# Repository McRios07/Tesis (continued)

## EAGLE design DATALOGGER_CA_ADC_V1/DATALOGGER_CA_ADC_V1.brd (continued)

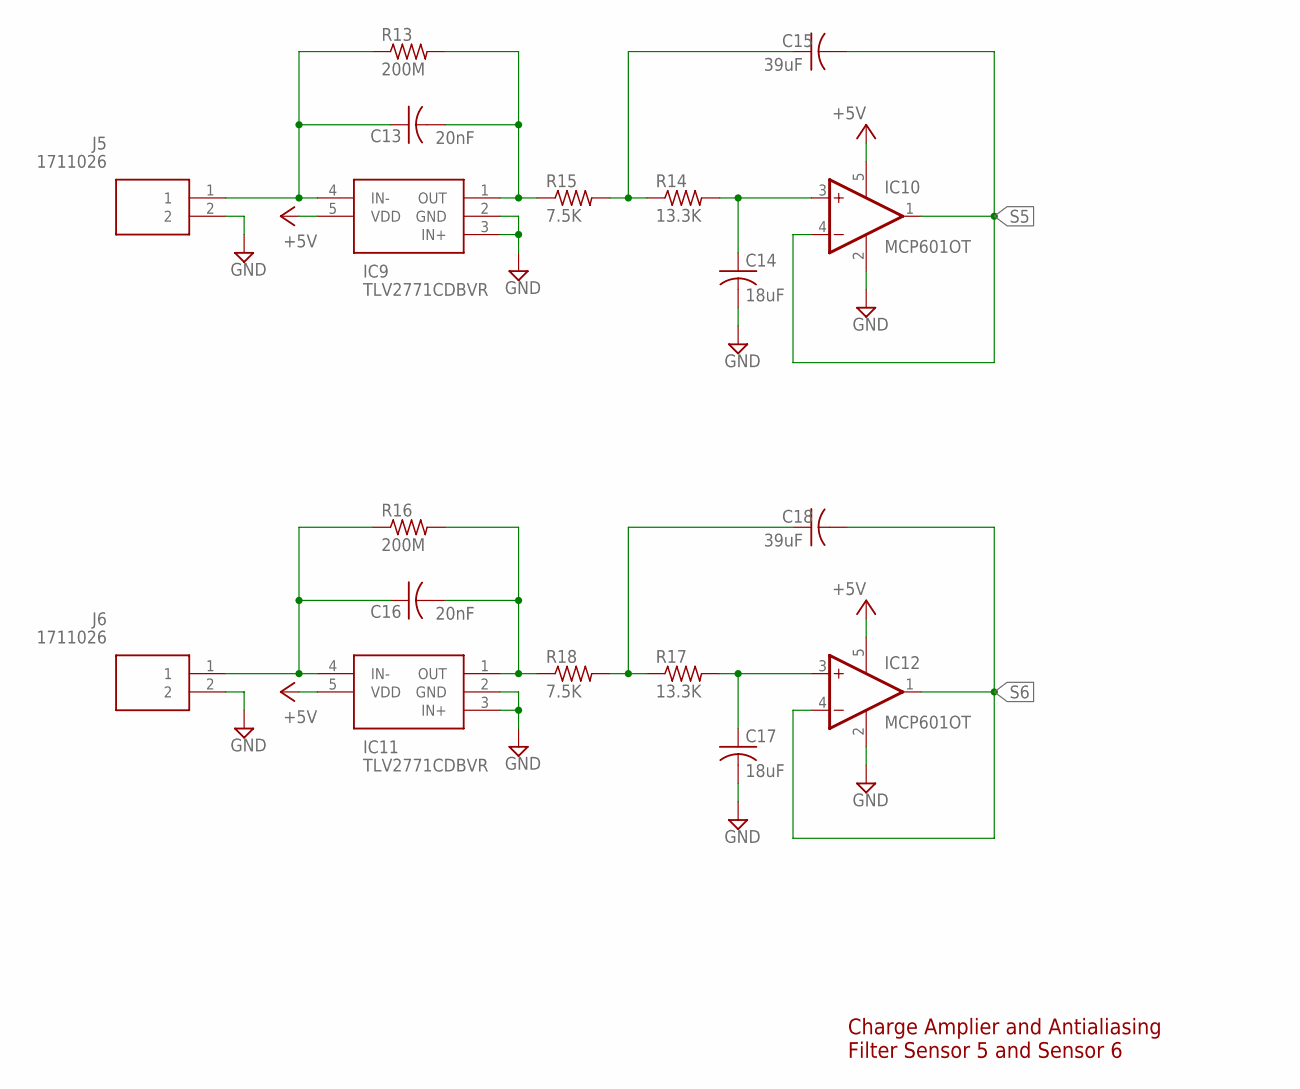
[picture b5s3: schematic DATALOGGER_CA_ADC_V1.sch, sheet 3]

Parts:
C13, C16: 20nF; C0805
C14, C17: 18uF; C0805
C15, C18: 39uF; C0805
IC9, IC11: TLV2771CDBVR; SOT95P280X145-5N
IC10, IC12: MCP601OT; SOT23-5
J5, J6: 1711026; SHDR2W110P0X500_1X2_1000X1120X
R13, R16: 200M; R0805
R14, R17: 13.3K; R0805
R15, R18: 7.5K; R0805

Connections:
+5V: IC9.5 (VDD), IC10.5 (V+), IC11.5 (VDD), IC12.5 (V+); also elsewhere on the board
GND: C14.2, C17.2, IC9.2 (GND), IC9.3 (IN+), IC10.2 (V-), IC11.2 (GND), IC11.3 (IN+), IC12.2 (V-), J5.2, J6.2; also elsewhere on the board
unnamed: C13.1, IC9.4 (IN-), J5.1, R13.1
unnamed: C13.2, IC9.1 (OUT), R13.2, R15.1
unnamed: C14.1, IC10.3 (+IN), R14.2
unnamed: C15.1, R14.1, R15.2
unnamed: C16.1, IC11.4 (IN-), J6.1, R16.1
unnamed: C16.2, IC11.1 (OUT), R16.2, R18.1
unnamed: C17.1, IC12.3 (+IN), R17.2
unnamed: C18.1, R17.1, R18.2
S5: C15.2, IC10.1 (OUT), IC10.4 (-IN); also elsewhere on the board
S6: C18.2, IC12.1 (OUT), IC12.4 (-IN); also elsewhere on the board

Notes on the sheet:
Charge Amplier and Antialiasing Filter Sensor 5 and Sensor 6

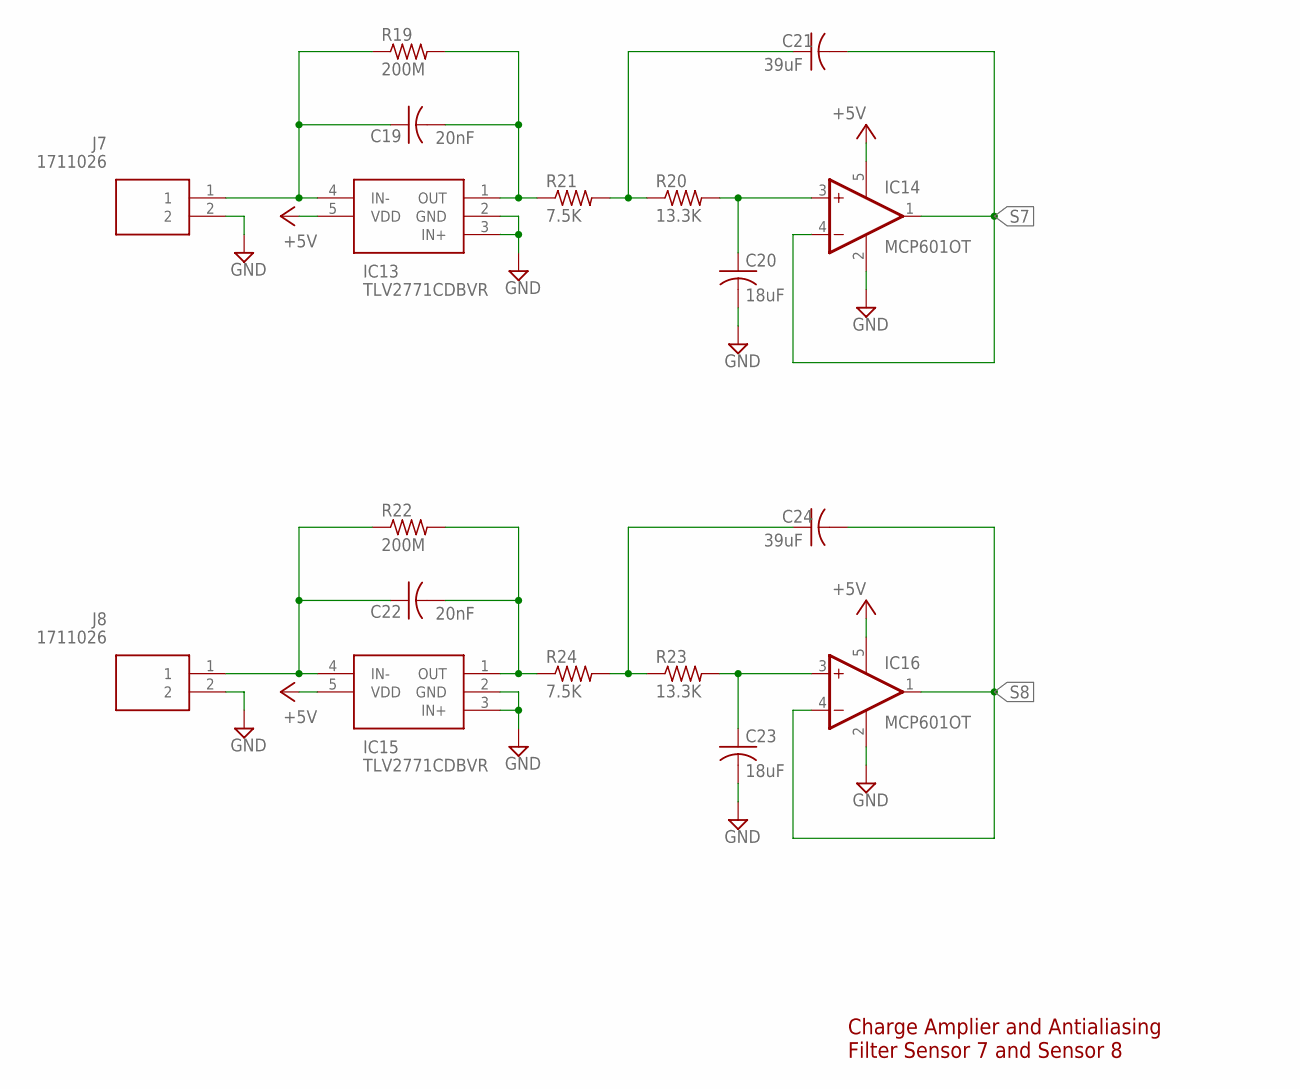
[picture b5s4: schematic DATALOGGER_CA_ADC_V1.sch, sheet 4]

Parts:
C19, C22: 20nF; C0805
C20, C23: 18uF; C0805
C21, C24: 39uF; C0805
IC13, IC15: TLV2771CDBVR; SOT95P280X145-5N
IC14, IC16: MCP601OT; SOT23-5
J7, J8: 1711026; SHDR2W110P0X500_1X2_1000X1120X
R19, R22: 200M; R0805
R20, R23: 13.3K; R0805
R21, R24: 7.5K; R0805

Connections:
+5V: IC13.5 (VDD), IC14.5 (V+), IC15.5 (VDD), IC16.5 (V+); also elsewhere on the board
GND: C20.2, C23.2, IC13.2 (GND), IC13.3 (IN+), IC14.2 (V-), IC15.2 (GND), IC15.3 (IN+), IC16.2 (V-), J7.2, J8.2; also elsewhere on the board
unnamed: C19.1, IC13.4 (IN-), J7.1, R19.1
unnamed: C19.2, IC13.1 (OUT), R19.2, R21.1
unnamed: C20.1, IC14.3 (+IN), R20.2
unnamed: C21.1, R20.1, R21.2
unnamed: C22.1, IC15.4 (IN-), J8.1, R22.1
unnamed: C22.2, IC15.1 (OUT), R22.2, R24.1
unnamed: C23.1, IC16.3 (+IN), R23.2
unnamed: C24.1, R23.1, R24.2
S7: C21.2, IC14.1 (OUT), IC14.4 (-IN); also elsewhere on the board
S8: C24.2, IC16.1 (OUT), IC16.4 (-IN); also elsewhere on the board

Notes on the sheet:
Charge Amplier and Antialiasing Filter Sensor 7 and Sensor 8

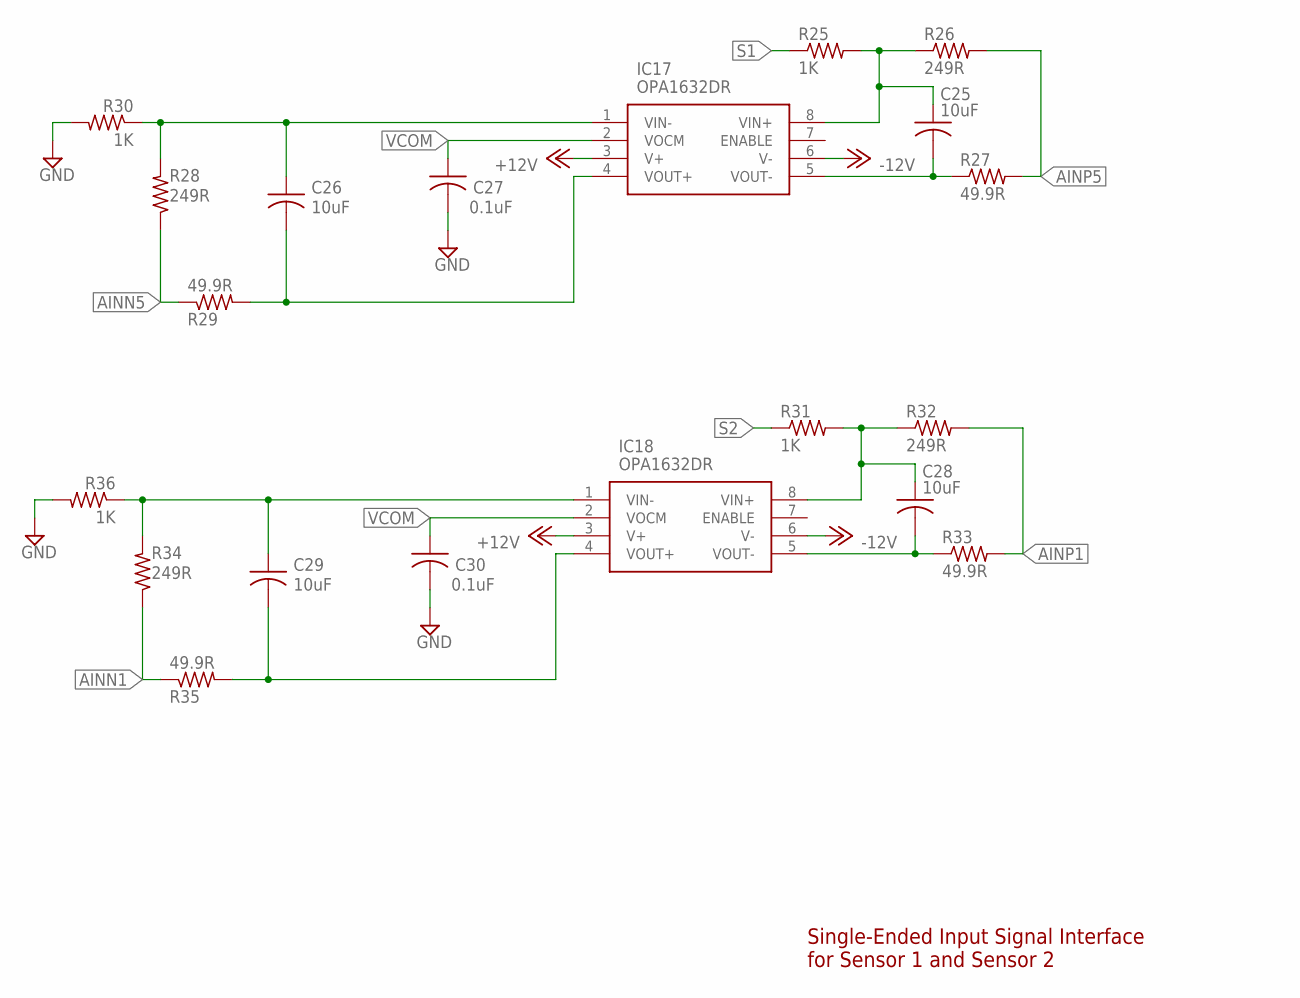
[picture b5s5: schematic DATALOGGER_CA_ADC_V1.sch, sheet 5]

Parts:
C25, C26, C28, C29: 10uF; C0805
C27, C30: 0.1uF; C0805
IC17, IC18: OPA1632DR; SOIC127P600X175-8N
R25, R30, R31, R36: 1K; R0805
R26, R28, R32, R34: 249R; R0805
R27, R29, R33, R35: 49.9R; R0805

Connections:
+12V: IC17.3 (V+), IC18.3 (V+); also elsewhere on the board
-12V: IC17.6 (V-), IC18.6 (V-); also elsewhere on the board
AINN1: R34.1, R35.1; also elsewhere on the board
AINN5: R28.1, R29.1; also elsewhere on the board
AINP1: R32.2, R33.2; also elsewhere on the board
AINP5: R26.2, R27.2; also elsewhere on the board
GND: C27.2, C30.2, R30.2, R36.2; also elsewhere on the board
unnamed: C25.1, IC17.8 (VIN+), R25.2, R26.1
unnamed: C25.2, IC17.5 (VOUT-), R27.1
unnamed: C26.1, IC17.1 (VIN-), R28.2, R30.1
unnamed: C28.1, IC18.8 (VIN+), R31.2, R32.1
unnamed: C26.2, IC17.4 (VOUT+), R29.2
unnamed: C28.2, IC18.5 (VOUT-), R33.1
unnamed: C29.1, IC18.1 (VIN-), R34.2, R36.1
unnamed: C29.2, IC18.4 (VOUT+), R35.2
S1: R25.1; also elsewhere on the board
S2: R31.1; also elsewhere on the board
VCOM: C27.1, C30.1, IC17.2 (VOCM), IC18.2 (VOCM); also elsewhere on the board

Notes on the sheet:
Single-Ended Input Signal Interface for Sensor 1 and Sensor 2

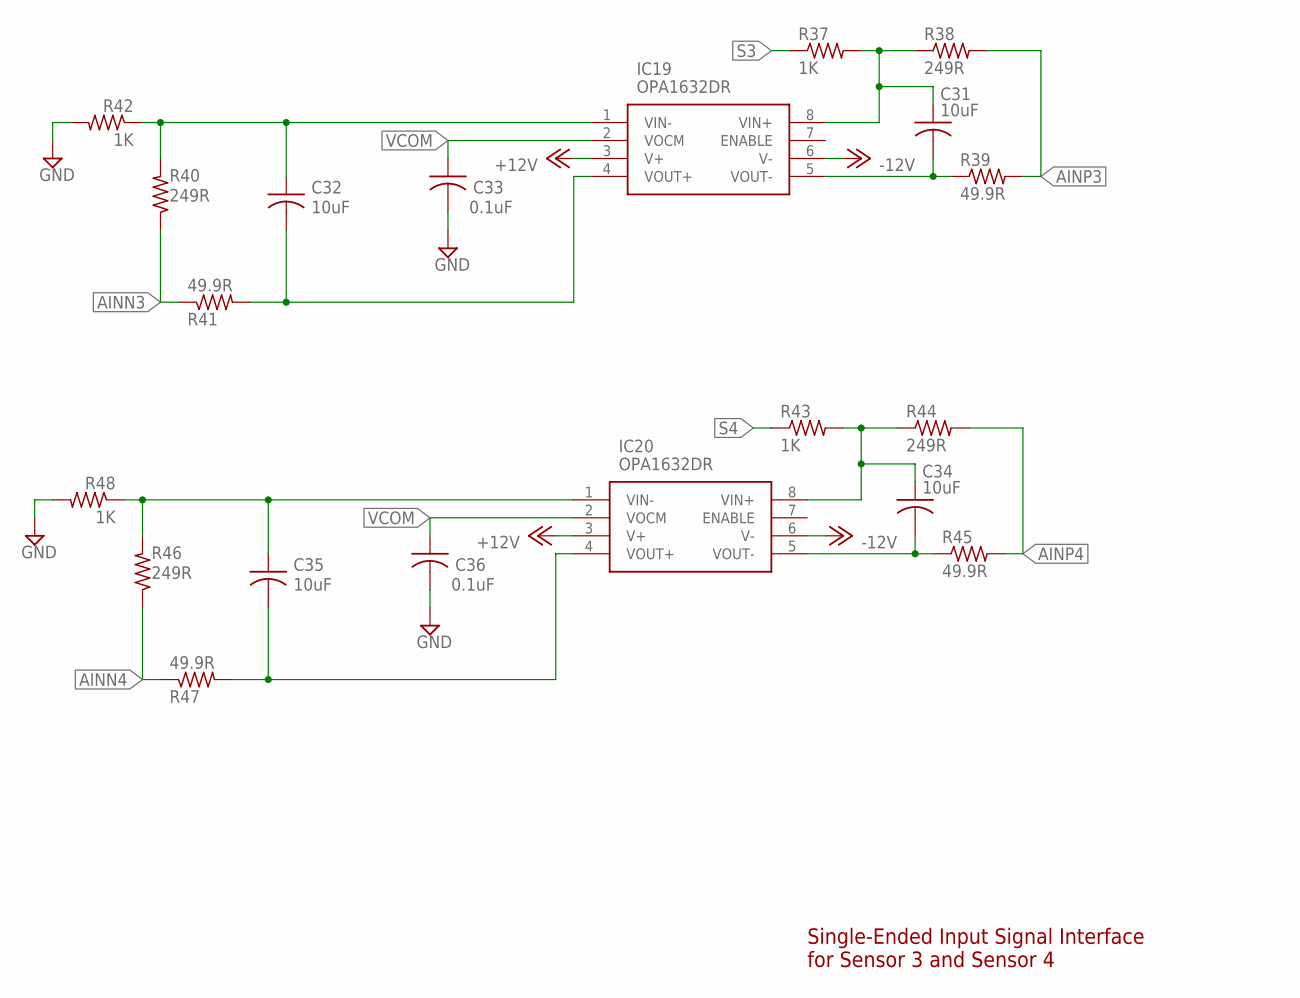
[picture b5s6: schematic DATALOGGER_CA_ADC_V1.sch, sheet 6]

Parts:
C31, C32, C34, C35: 10uF; C0805
C33, C36: 0.1uF; C0805
IC19, IC20: OPA1632DR; SOIC127P600X175-8N
R37, R42, R43, R48: 1K; R0805
R38, R40, R44, R46: 249R; R0805
R39, R41, R45, R47: 49.9R; R0805

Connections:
+12V: IC19.3 (V+), IC20.3 (V+); also elsewhere on the board
-12V: IC19.6 (V-), IC20.6 (V-); also elsewhere on the board
AINN3: R40.1, R41.1; also elsewhere on the board
AINN4: R46.1, R47.1; also elsewhere on the board
AINP3: R38.2, R39.2; also elsewhere on the board
AINP4: R44.2, R45.2; also elsewhere on the board
GND: C33.2, C36.2, R42.2, R48.2; also elsewhere on the board
unnamed: C31.1, IC19.8 (VIN+), R37.2, R38.1
unnamed: C31.2, IC19.5 (VOUT-), R39.1
unnamed: C32.1, IC19.1 (VIN-), R40.2, R42.1
unnamed: C32.2, IC19.4 (VOUT+), R41.2
unnamed: C34.1, IC20.8 (VIN+), R43.2, R44.1
unnamed: C34.2, IC20.5 (VOUT-), R45.1
unnamed: C35.1, IC20.1 (VIN-), R46.2, R48.1
unnamed: C35.2, IC20.4 (VOUT+), R47.2
S3: R37.1; also elsewhere on the board
S4: R43.1; also elsewhere on the board
VCOM: C33.1, C36.1, IC19.2 (VOCM), IC20.2 (VOCM); also elsewhere on the board

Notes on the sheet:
Single-Ended Input Signal Interface for Sensor 3 and Sensor 4

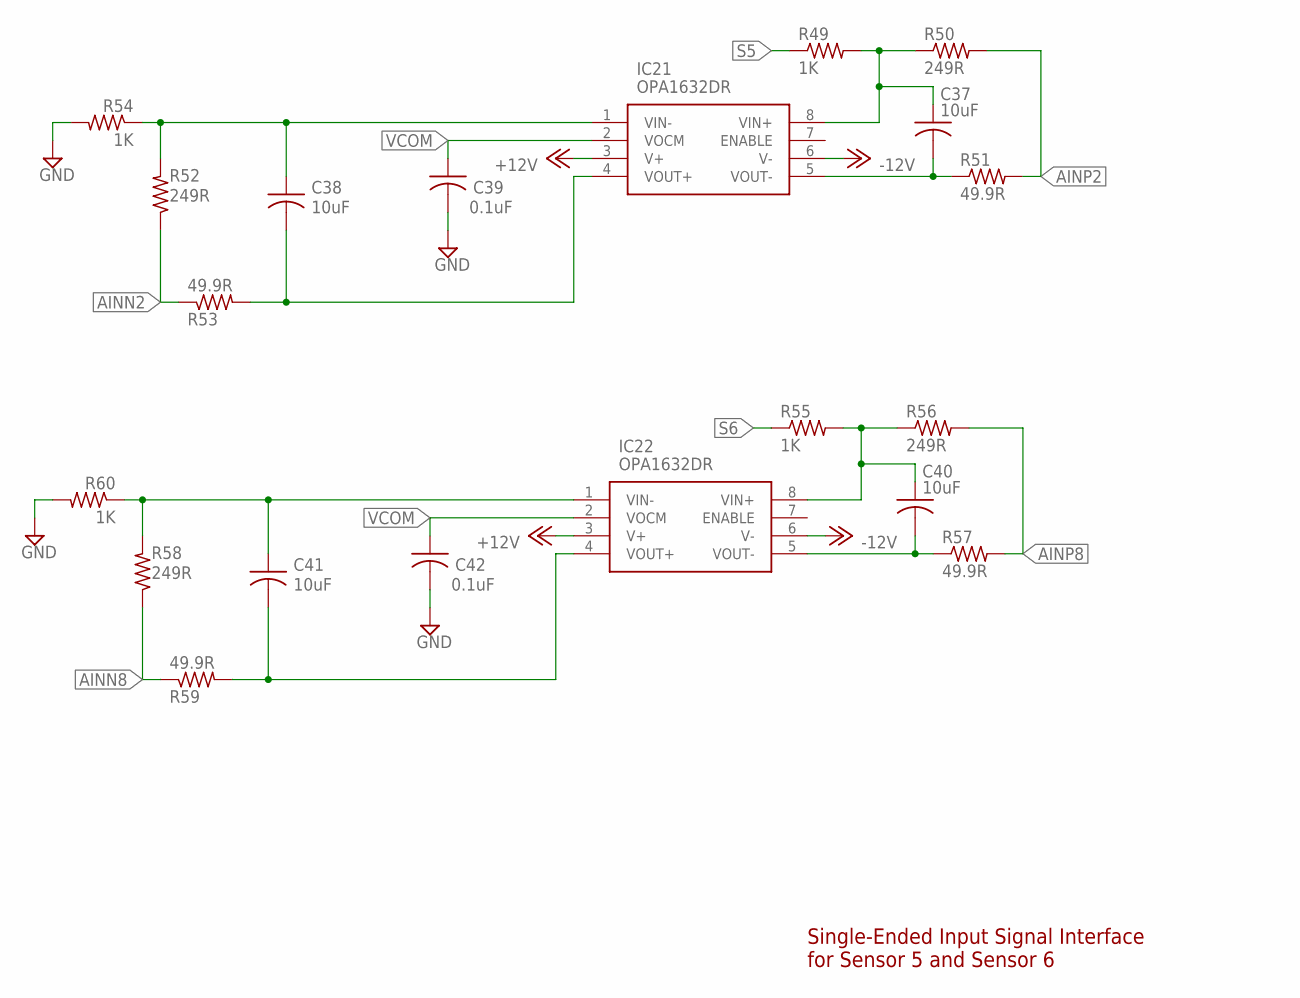
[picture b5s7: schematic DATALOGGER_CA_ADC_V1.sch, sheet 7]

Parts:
C37, C38, C40, C41: 10uF; C0805
C39, C42: 0.1uF; C0805
IC21, IC22: OPA1632DR; SOIC127P600X175-8N
R49, R54, R55, R60: 1K; R0805
R50, R52, R56, R58: 249R; R0805
R51, R53, R57, R59: 49.9R; R0805

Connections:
+12V: IC21.3 (V+), IC22.3 (V+); also elsewhere on the board
-12V: IC21.6 (V-), IC22.6 (V-); also elsewhere on the board
AINN2: R52.1, R53.1; also elsewhere on the board
AINN8: R58.1, R59.1; also elsewhere on the board
AINP2: R50.2, R51.2; also elsewhere on the board
AINP8: R56.2, R57.2; also elsewhere on the board
GND: C39.2, C42.2, R54.2, R60.2; also elsewhere on the board
unnamed: C37.1, IC21.8 (VIN+), R49.2, R50.1
unnamed: C37.2, IC21.5 (VOUT-), R51.1
unnamed: C38.1, IC21.1 (VIN-), R52.2, R54.1
unnamed: C38.2, IC21.4 (VOUT+), R53.2
unnamed: C40.1, IC22.8 (VIN+), R55.2, R56.1
unnamed: C40.2, IC22.5 (VOUT-), R57.1
unnamed: C41.1, IC22.1 (VIN-), R58.2, R60.1
unnamed: C41.2, IC22.4 (VOUT+), R59.2
S5: R49.1; also elsewhere on the board
S6: R55.1; also elsewhere on the board
VCOM: C39.1, C42.1, IC21.2 (VOCM), IC22.2 (VOCM); also elsewhere on the board

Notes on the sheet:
Single-Ended Input Signal Interface for Sensor 5 and Sensor 6

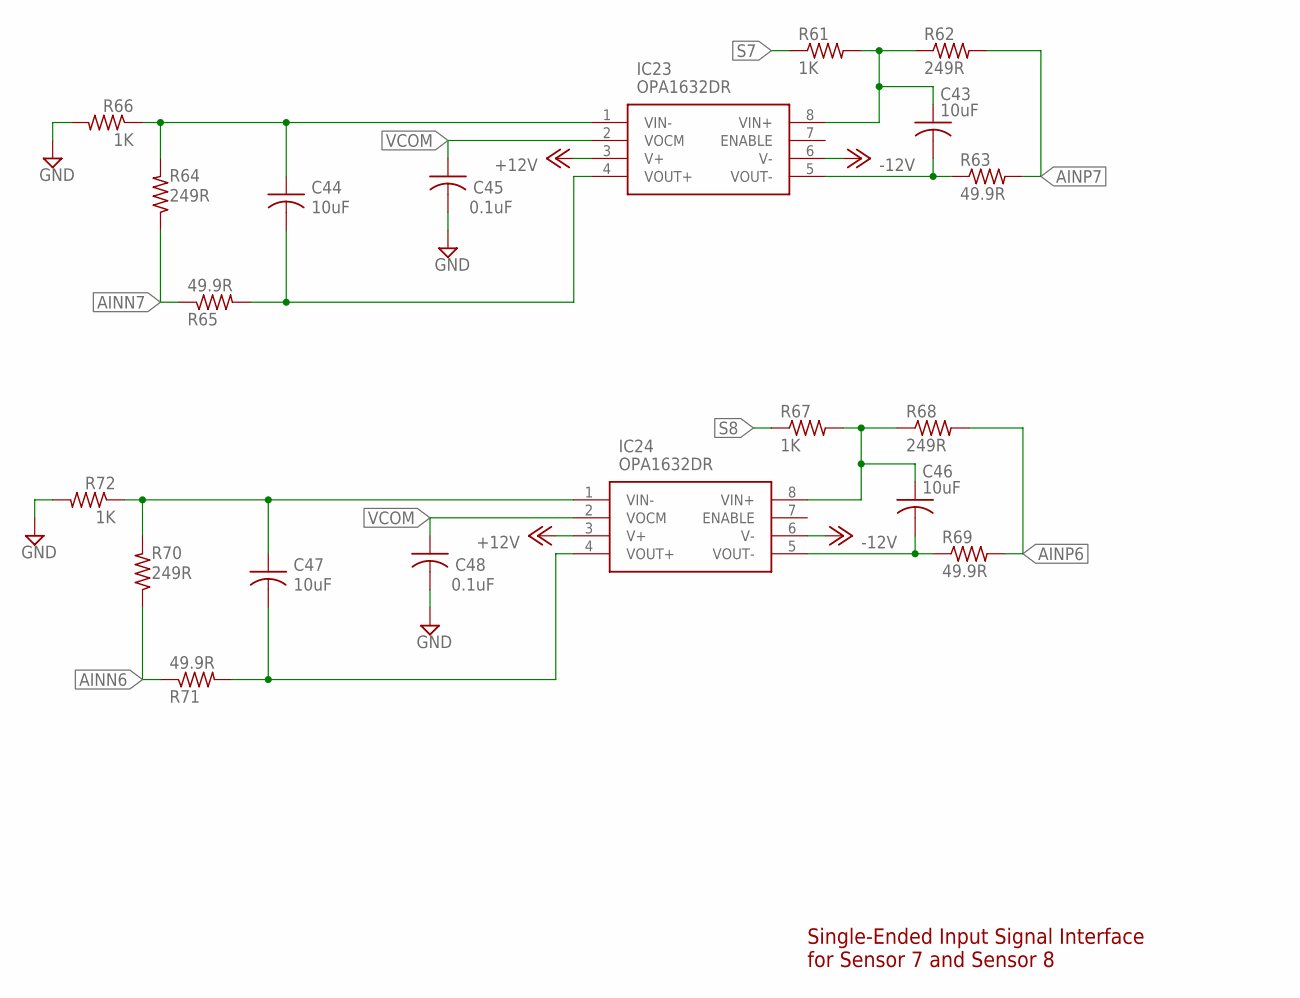
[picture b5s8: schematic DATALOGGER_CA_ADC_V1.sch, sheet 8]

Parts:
C43, C44, C46, C47: 10uF; C0805
C45, C48: 0.1uF; C0805
IC23, IC24: OPA1632DR; SOIC127P600X175-8N
R61, R66, R67, R72: 1K; R0805
R62, R64, R68, R70: 249R; R0805
R63, R65, R69, R71: 49.9R; R0805

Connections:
+12V: IC23.3 (V+), IC24.3 (V+); also elsewhere on the board
-12V: IC23.6 (V-), IC24.6 (V-); also elsewhere on the board
AINN6: R70.1, R71.1; also elsewhere on the board
AINN7: R64.1, R65.1; also elsewhere on the board
AINP6: R68.2, R69.2; also elsewhere on the board
AINP7: R62.2, R63.2; also elsewhere on the board
GND: C45.2, C48.2, R66.2, R72.2; also elsewhere on the board
unnamed: C43.1, IC23.8 (VIN+), R61.2, R62.1
unnamed: C43.2, IC23.5 (VOUT-), R63.1
unnamed: C44.1, IC23.1 (VIN-), R64.2, R66.1
unnamed: C44.2, IC23.4 (VOUT+), R65.2
unnamed: C46.1, IC24.8 (VIN+), R67.2, R68.1
unnamed: C46.2, IC24.5 (VOUT-), R69.1
unnamed: C47.1, IC24.1 (VIN-), R70.2, R72.1
unnamed: C47.2, IC24.4 (VOUT+), R71.2
S7: R61.1; also elsewhere on the board
S8: R67.1; also elsewhere on the board
VCOM: C45.1, C48.1, IC23.2 (VOCM), IC24.2 (VOCM); also elsewhere on the board

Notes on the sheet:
Single-Ended Input Signal Interface for Sensor 7 and Sensor 8

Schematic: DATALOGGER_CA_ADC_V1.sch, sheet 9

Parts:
JP1, JP2: PINHD-2X10; 2X10

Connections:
+1V8: JP1.19, JP1.20; also elsewhere on the board
+3V3: JP1.17, JP1.18; also elsewhere on the board
+5V: JP1.13, JP1.14; also elsewhere on the board
+12V: JP1.1, JP1.2; also elsewhere on the board
+24V: JP1.9, JP1.10
-12V: JP1.5, JP1.6; also elsewhere on the board
CLK: JP2.9; also elsewhere on the board
DOUT1: JP2.10; also elsewhere on the board
DOUT2: JP2.7; also elsewhere on the board
DOUT3: JP2.8; also elsewhere on the board
DOUT4: JP2.5; also elsewhere on the board
DOUT5: JP2.6; also elsewhere on the board
DOUT6: JP2.3; also elsewhere on the board
DOUT7: JP2.4; also elsewhere on the board
DOUT8: JP2.1; also elsewhere on the board
DRDY: JP2.11; also elsewhere on the board
GND: JP1.3, JP1.4, JP1.7, JP1.8, JP1.11, JP1.12, JP1.15, JP1.16, JP2.13, JP2.14, JP2.15, JP2.16, JP2.17, JP2.18, JP2.19, JP2.20; also elsewhere on the board
SCLK: JP2.12; also elsewhere on the board
SYNC: JP2.2; also elsewhere on the board

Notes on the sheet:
Inputs and Outputs

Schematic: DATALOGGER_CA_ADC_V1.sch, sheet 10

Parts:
C49: 100uF; C1206
C50, C51, C53, C54: 0.1uF; C0805
C52: 10uF; C0805
C55, C56, C57, C58, C59, C60, C61, C62: 2.2nF; C0805
IC25: REF1004U; SO08
R73: 20K; R0805
R74, R76: 1K; R0805
R75, R77, R78: 100R; R0805
U1, U2: OPA350EA/2K5; DGK8_TEX

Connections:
+5V: R73.2, U1.7 (V+), U2.7 (V+); also elsewhere on the board
AINN1: C55.2; also elsewhere on the board
AINN2: C56.2; also elsewhere on the board
AINN3: C57.2; also elsewhere on the board
AINN4: C58.2; also elsewhere on the board
AINN5: C59.2; also elsewhere on the board
AINN6: C60.2; also elsewhere on the board
AINN7: C61.2; also elsewhere on the board
AINN8: C62.2; also elsewhere on the board
AINP1: C55.1; also elsewhere on the board
AINP2: C56.1; also elsewhere on the board
AINP3: C57.1; also elsewhere on the board
AINP4: C58.1; also elsewhere on the board
AINP5: C59.1; also elsewhere on the board
AINP6: C60.1; also elsewhere on the board
AINP7: C61.1; also elsewhere on the board
AINP8: C62.1; also elsewhere on the board
GND: C49.2, C50.2, C52.2, C53.2, C54.2, IC25.4 (A), U1.4 (V-), U2.4 (V-); also elsewhere on the board
unnamed: IC25.8 (C1), R73.1
unnamed: IC25.6 (C), R74.1
unnamed: C49.1, C50.1, R74.2, R75.1
unnamed: R75.2, U2.3 (IN+)
unnamed: C51.2, R77.1, U2.6 (OUTPUT)
unnamed: C51.1, R76.1, U2.2 (IN-)
unnamed: R78.1, U1.2 (IN-), U1.6 (OUTPUT)
VCOM: R78.2; also elsewhere on the board
VCOMM: C54.1, U1.3 (IN+); also elsewhere on the board
VREFP: C52.1, C53.1, R76.2, R77.2; also elsewhere on the board

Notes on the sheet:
Voltage References for ADS

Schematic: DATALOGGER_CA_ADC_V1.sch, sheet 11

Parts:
C63, C64, C65: 10uF; C0805
SJ1: SJ2W; SJ_2
U3: ADS1178IPAPT; PAP64_TEX

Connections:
+1V8: C65.1, U3.26 (DVDD); also elsewhere on the board
+3V3: C64.1, SJ1.1, U3.10 (CLKDIV), U3.22 (IOVDD_2), U3.23 (IOVDD), U3.31 (FORMAT1); also elsewhere on the board
+5V: C63.1, U3.5 (AVDD_2), U3.44 (AVDD_3), U3.60 (AVDD); also elsewhere on the board
AINN1: U3.4 (AINN1); also elsewhere on the board
AINN2: U3.2 (AINN2); also elsewhere on the board
AINN3: U3.64 (AINN3); also elsewhere on the board
AINN4: U3.62 (AINN4); also elsewhere on the board
AINN5: U3.52 (AINN5); also elsewhere on the board
AINN6: U3.50 (AINN6); also elsewhere on the board
AINN7: U3.48 (AINN7); also elsewhere on the board
AINN8: U3.46 (AINN8); also elsewhere on the board
AINP1: U3.3 (AINP1); also elsewhere on the board
AINP2: U3.1 (AINP2); also elsewhere on the board
AINP3: U3.63 (AINP3); also elsewhere on the board
AINP4: U3.61 (AINP4); also elsewhere on the board
AINP5: U3.51 (AINP5); also elsewhere on the board
AINP6: U3.49 (AINP6); also elsewhere on the board
AINP7: U3.47 (AINP7); also elsewhere on the board
AINP8: U3.45 (AINP8); also elsewhere on the board
CLK: U3.27 (CLK); also elsewhere on the board
DOUT1: U3.20 (DOUT1); also elsewhere on the board
DOUT2: U3.19 (DOUT2); also elsewhere on the board
DOUT3: U3.18 (DOUT3); also elsewhere on the board
DOUT4: U3.17 (DOUT4); also elsewhere on the board
DOUT5: U3.16 (DOUT5); also elsewhere on the board
DOUT6: U3.15 (DOUT6); also elsewhere on the board
DOUT7: U3.14 (DOUT7); also elsewhere on the board
DOUT8: U3.13 (DOUT8); also elsewhere on the board
DRDY: U3.29 (!DRDY/FSYNC); also elsewhere on the board
GND: C63.2, C64.2, C65.2, SJ1.3, U3.6 (AGND_2), U3.7 (DGND_2), U3.8 (TEST0), U3.9 (TEST1), U3.12 (DIN), U3.21 (DGND_3), U3.24 (DGND_4), U3.25 (DGND), U3.30 (FORMAT2), U3.32 (FORMAT0), U3.34 (MODE), U3.43 (AGND_3), U3.53 (AVDD_4), U3.54 (AGND_4), U3.57 (VREFN), U3.58 (AGND_5), U3.59 (AGND), U3.EPAD; also elsewhere on the board
unnamed: SJ1.2, U3.35 (!PWDN8), U3.36 (!PWDN7), U3.37 (!PWDN6), U3.38 (!PWDN5), U3.39 (!PWDN4), U3.40 (!PWDN3), U3.41 (!PWDN2), U3.42 (!PWDN1)
SCLK: U3.28 (SCLK); also elsewhere on the board
SYNC: U3.11 (!SYNC); also elsewhere on the board
VCOMM: U3.55 (VCOM); also elsewhere on the board
VREFP: U3.56 (VREFP); also elsewhere on the board

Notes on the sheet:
ADS connection

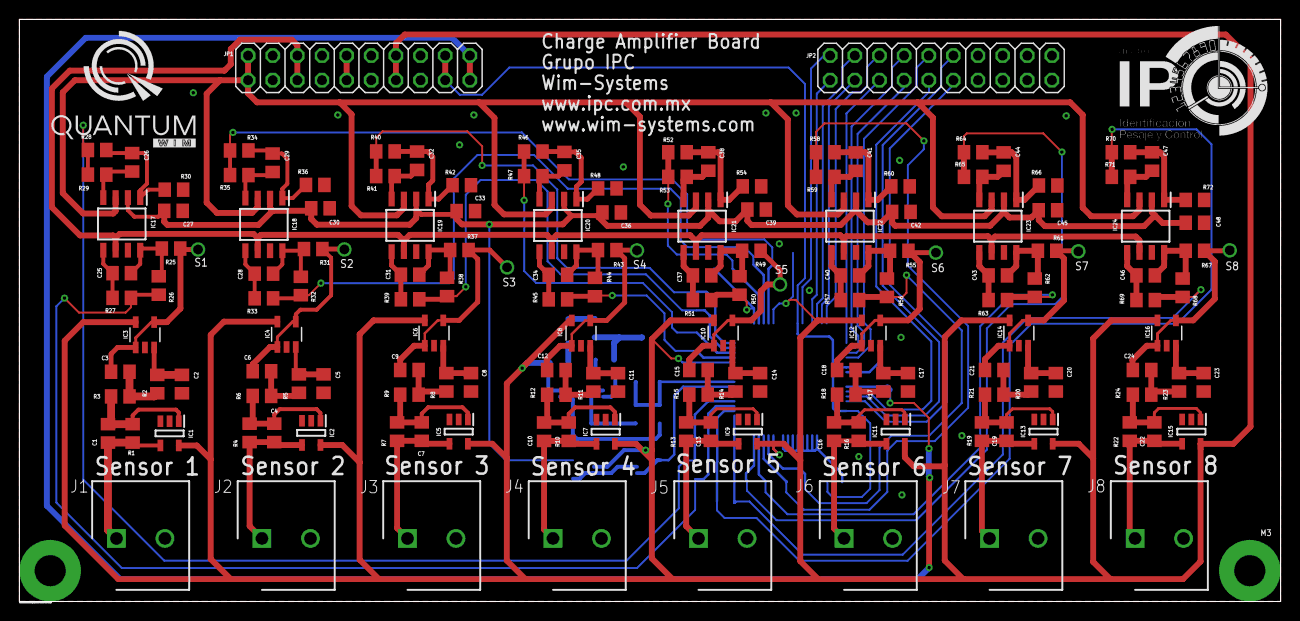
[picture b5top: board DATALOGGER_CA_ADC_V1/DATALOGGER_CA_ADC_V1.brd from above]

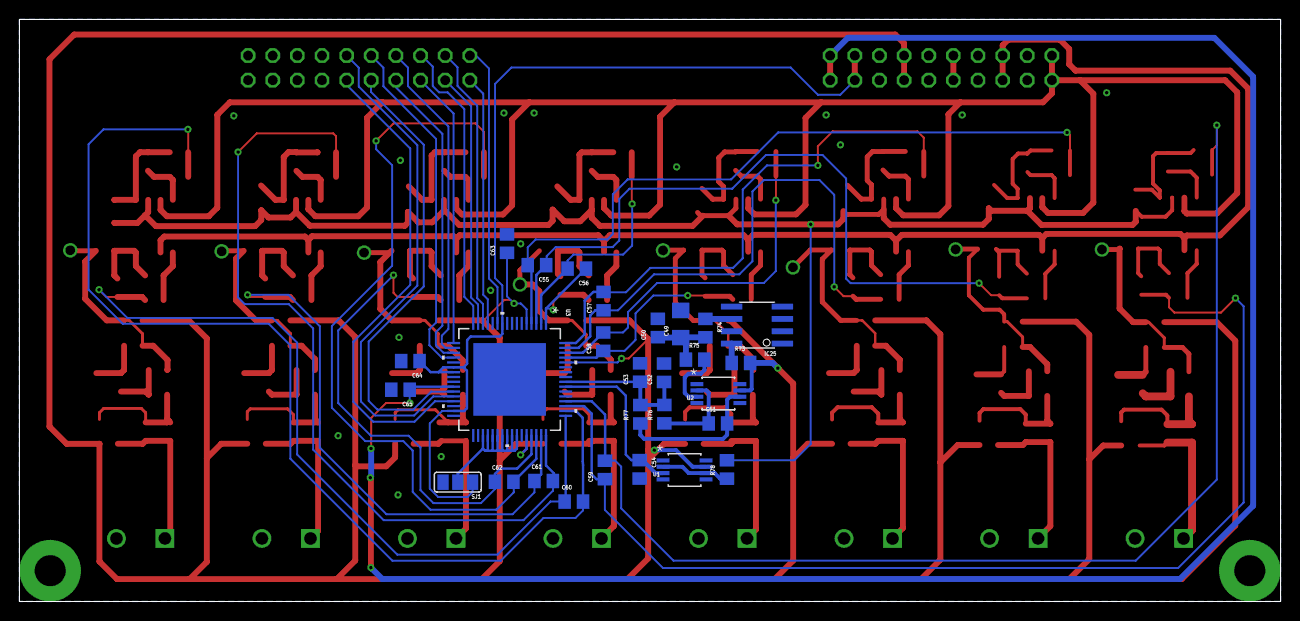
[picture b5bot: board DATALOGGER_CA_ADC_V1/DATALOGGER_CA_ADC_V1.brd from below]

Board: 2 copper layers, 130.0 x 60.0 mm, 182 parts (28 on the bottom side), 118 nets.

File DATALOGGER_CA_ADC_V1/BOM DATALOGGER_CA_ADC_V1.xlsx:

|  |  | BOM DATALOGGER_CA_ADC_V1 (Sample Bill of Materials)
Item # | *Designator | *Qty | Manufacturer | *Mfg Part # | Description / Value | *Package/Footprint | Type | Your Instructions / Notes
1 | JP1 | 1 |  | SFH11-PBPC-D10-RA-BK | 20 Position Header Connector Through Hole, Right Angle | 2X10 | Through Hole
2 | JP2 | 1 |  | ESQ-110-14-T-D | 20 Position Elevated Socket Connector Through Hole | 2X10 | Through Hole
3 | SJ1 | 1 |  |  |  |  |  | no device connected
4 | C27, C30, C33, C36, C39, C42, C45, C48, C50, C51, C53, C54 | 12 |  | Generic | 0.1µF ±10% 50V Ceramic Capacitor X7R 0805 (2012 Metric) | 0805 | SMD
5 | R75, R77, R78 | 3 |  | Generic | 100 Ohms ±0.1% 0.125W, 1/8W Chip Resistor 0805 (2012 Metric) Automotive AEC-Q20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 | 0805 | SMD
6 | C49 | 1 |  | Generic | 100µF ±20% 4V Ceramic Capacitor X6S 0805 (2012 Metric) | 1206 | SMD
7 | C25, C26, C28, C29, C31, C32, C34, C35, C37, C38, C40, C41, C43, C44, C46, C47,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 | 20 |  | Generic | 10µF ±10% 6.3V Ceramic Capacitor X5R 0805 (2012 Metric) | 0805 | SMD
8 | R2, R5, R8, R11, R14, R17, R20, R23 | 8 |  | RC0805FR-0713K3L | 13.3 kOhms ±1% 0.125W, 1/8W Chip Resistor 0805 (2012 Metric) Moisture Resistant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 | 0805 | SMD
9 | J1, J2, J3, J4, J5, J6, J7, J8 | 8 |  | 1711026 | 2 Position Wire to Board Terminal Block Horizontal with Board 0.197" (5.00mm) T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 | 1711026 | Through Hole
10 | C2, C5, C8, C11, C14, C17, C20, C23 | 8 |  | C0805C183K5RACTU | 0.018µF ±10% 50V Ceramic Capacitor X7R 0805 (2012 Metric) | 0805 | SMD
11 | R25, R30, R31, R36, R37, R42, R43, R48, R49, R54, R55, R60, R61, R66, R67, R72,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 | 18 |  | Generic | 1 kOhms ±1% 0.125W, 1/8W Chip Resistor 0805 (2012 Metric) Moisture Resistant Th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 | 0805 | SMD
12 | C55, C56, C57, C58, C59, C60, C61, C62 | 8 |  | GRM2165C1H222JA01D | 2200pF ±5% 50V Ceramic Capacitor C0G, NP0 0805 (2012 Metric) | 0805 | SMD
13 | R1, R4, R7, R10, R13, R16, R19, R22 | 8 |  | HMC0805JT200M | 200 MOhms ±5% 0.125W, 1/8W Chip Resistor 0805 (2012 Metric) Thick Film | 0805 | SMD
14 | R73 | 1 |  | Generic | 20 kOhms ±1% 0.125W, 1/8W Chip Resistor 0805 (2012 Metric) Moisture Resistant T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 | 0805 | SMD
15 | C1, C4, C7, C10, C13, C16, C19, C22 | 8 |  | Generic | 0.02µF ±5% 50V Ceramic Capacitor C0G, NP0 0805 (2012 Metric) | 0805 | SMD
16 | R26, R28, R32, R34, R38, R40, R44, R46, R50, R52, R56, R58, R62, R64, R68, R70 | 16 |  | RC0805FR-07249RL | 249 Ohms ±1% 0.125W, 1/8W Chip Resistor 0805 (2012 Metric) Moisture Resistant T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 | 0805 | SMD
17 | C3, C6, C9, C12, C15, C18, C21, C24 | 8 |  | C0805C393J5RACTU | 0.039µF ±5% 50V Ceramic Capacitor X7R 0805 (2012 Metric) | 0805 | SMD
18 | R27, R29, R33, R35, R39, R41, R45, R47, R51, R53, R57, R59, R63, R65, R69, R71 | 16 |  | ERJ-6ENF49R9V | 49.9 Ohms ±1% 0.125W, 1/8W Chip Resistor 0805 (2012 Metric) Automotive AEC-Q200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 | 0805 | SMD
19 | R3, R6, R9, R12, R15, R18, R21, R24 | 8 |  | CRG0805F7K5 | 7.5 kOhms ±1% 0.125W, 1/8W Chip Resistor 0805 (2012 Metric) Thick Film | 0805 | SMD
20 | U3 | 1 |  | ADS1178IPAPT | 16 Bit Analog to Digital Converter 8 Input 1 Sigma-Delta 64-HTQFP (10x10) | 64-HTQFP | SMD
21 | IC3, IC4, IC6, IC8, IC10, IC12, IC14, IC16 | 8 |  | MCP601T-I/OT | General Purpose Amplifier 1 Circuit Rail-to-Rail SOT-23-5 | SOT-23-5 | SMD
22 | IC17, IC18, IC19, IC20, IC21, IC22, IC23, IC24 | 8 |  | OPA1632DR | Audio Amplifier 1 Circuit Differential 8-SOIC | 8-SOIC | SMD
23 | U1, U2 | 2 |  | OPA350EA/2K5 | General Purpose Amplifier 1 Circuit Rail-to-Rail 8-VSSOP | 8-VSSOP | SMD
24 | IC25 | 1 |  | REF1004C-2.5 | Shunt Voltage Reference IC ±0.4% 8-SOIC | 8-SOIC | SMD
25 | IC1, IC2, IC5, IC7, IC9, IC11, IC13, IC15 | 8 |  | TLV2771CDBVR | General Purpose Amplifier 1 Circuit Rail-to-Rail SOT-23-5 | SOT-23-5 | SMD

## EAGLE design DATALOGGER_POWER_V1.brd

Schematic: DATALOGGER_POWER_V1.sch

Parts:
C1: 470uF; E5-13
C2: 1000uF; CAP_UCD_16X16P5_NCH
C3: 10uF; C1206
C4: 3.3uF; E2-4
C5, C7, C9: 10 uF; C1206
C6, C10: 390uF; E2-4
C8: 100 nF; C1206
D1: 1N5819-B; DO41-7.6
D2: LEDCHIPLED_1206; CHIPLED_1206
IC1: MIC4576-5.0WT; TO170P470X1016X1600-5P
IC2: TMH2412D
J1: +24V; SHDR2W110P0X500_1X2_1000X1120X
L1: 33uH; HCMA1707-330-R
L2, L3: 4.7uH; SRN4018
PS1: PAM2306AYPKE; SON45P300X300X80-13N
R1, R3: 0R; R1206
R2: 330; R1206
R5: 100K; R1206
SV1: MA10-2

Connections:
+1V8: C5.1, L2.2, R1.1, SV1.19, SV1.20
+3V3: C7.1, L3.2, R3.2, SV1.17, SV1.18
+5V: C2.1, C3.1, C9.1, IC1.4 (FB), L1.2, PS1.1 (VIN2), PS1.6 (EN1), PS1.7 (VIN1), R2.1, R5.1, SV1.13, SV1.14
+12V: C6.+, IC2.6 (+VOUT), SV1.1, SV1.2
+24V: C1.+, C4.+, IC1.1 (VIN), IC2.1 (VCC), J1.1, SV1.9, SV1.10
-12V: C10.+, IC2.4 (-VOUT), SV1.5, SV1.6
GND: C1.-, C2.2, C3.2, C4.-, C5.2, C6.-, C7.2, C8.2, C9.2, C10.-, D1.A, D2.C, IC1.3 (GND), IC1.5 (SHDN), IC2.2 (GND), IC2.5 (COM), J1.2, PS1.3 (GND_1), PS1.9 (GND_2), PS1.13 (GND_3), SV1.3, SV1.4, SV1.7, SV1.8, SV1.11, SV1.12, SV1.15, SV1.16
unnamed: D2.A, R2.2
unnamed: D1.C, IC1.2 (SW), L1.1
unnamed: L3.1, PS1.8 (LX1)
unnamed: L2.1, PS1.2 (LX2)
unnamed: PS1.10 (FB2), R1.2
unnamed: PS1.4 (FB1), R3.1
unnamed: C8.1, PS1.12 (EN2), R5.2

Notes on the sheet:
POWER SUPPLY

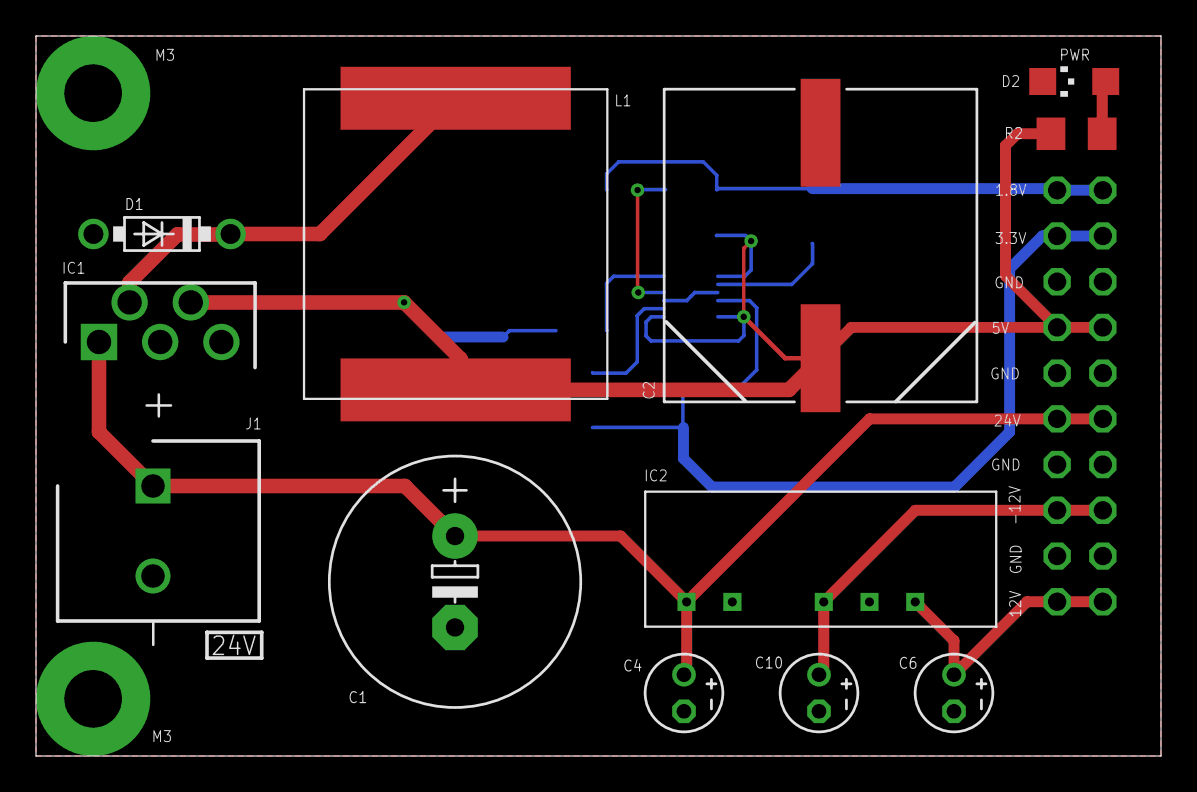
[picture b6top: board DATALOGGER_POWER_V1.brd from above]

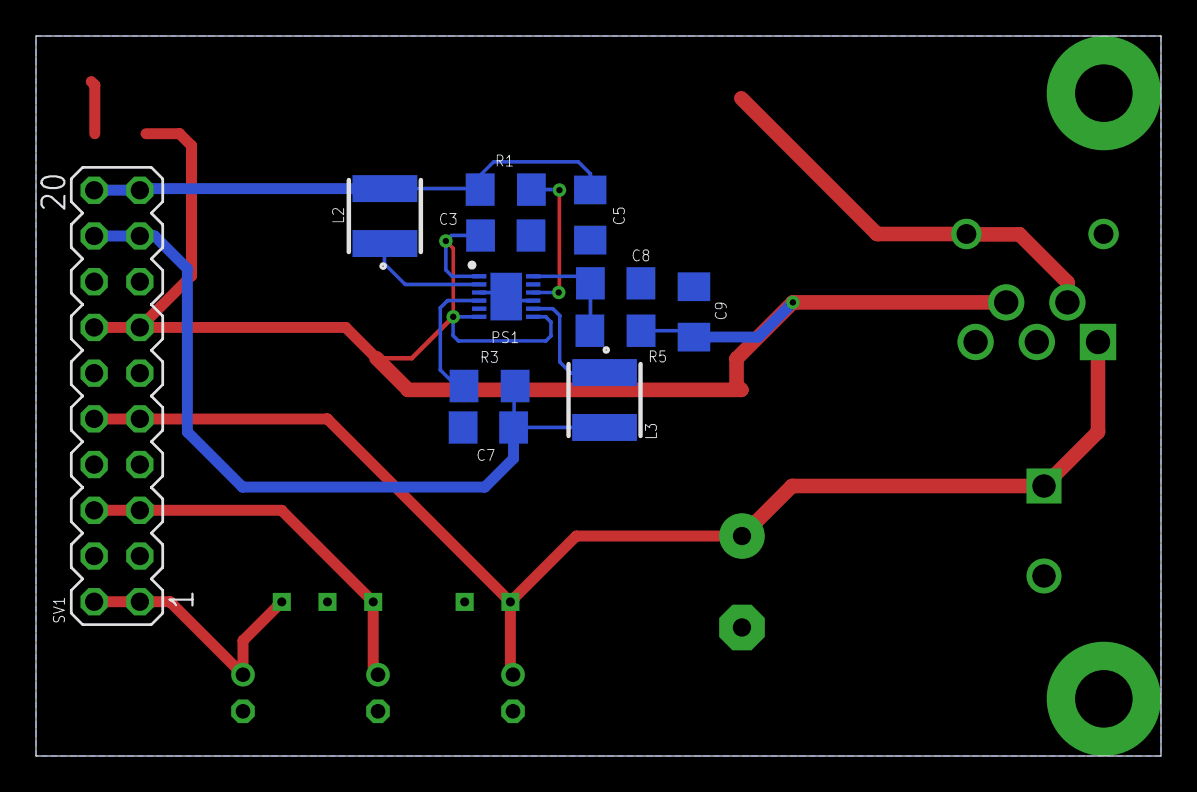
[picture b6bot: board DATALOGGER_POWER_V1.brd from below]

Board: 2 copper layers, 62.5 x 40.0 mm, 24 parts (12 on the bottom side), 14 nets.

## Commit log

2020-03-05 Subir archivos
    Primer commit
2020-03-05 Crear documento centiprod
2020-03-06 Acualización documento
2020-03-09 modifyPlant
2020-03-10 deletePlanta
2020-03-10 update all files
2020-03-10 spiAdded
2020-03-10 newGUI
2020-03-10 VentanaConfiguracion
2020-03-11 timer
2020-03-12 calibracion
2020-03-13 monitoreo
2020-03-13 adquisicion
2020-06-19 tarjetas
2020-08-02 comentarios
2020-08-03 mas comntarios
2020-09-18 matlab
2020-09-23 modify
2020-10-20 calibration
2020-10-21 calibrando_raspberry
2020-10-21 avance
2020-10-26 weekend
2020-10-27 jaral
2020-10-28 calibrar
2021-01-05 fin ipc
2021-01-05 de1 soc
2021-01-27 LIBRARY
    EAGLE
2021-01-27 tarjetav1
2021-01-28 tarjeta_v2
2021-01-28 tarjeta_v3
2021-01-29 tarjeta_v4
2021-02-02 tarjeta_v5
2021-02-02 tarjeta_v6
2021-02-03 tarjeta_v7
2021-02-04 tarjeta_v8
2021-02-05 tarjeta_v9
2021-02-05 tarjeta_v10
2021-02-08 tarjeta_v11
2021-02-08 tarjeta_v12
2021-02-09 tarjeta_v13
2021-02-10 tarjeta_v14
2021-02-12 tarjeta_v15
2021-02-17 tarjeta_v16
2021-02-23 tarjeta_v17
2021-03-12 tarjeta_v18
2021-03-16 tarjeta_v19
2021-03-18 TARJETA_V20
2021-03-19 tarjeta_v21
2021-03-22 tarjeta_v22
2021-03-26 datalogger
2021-03-27 datlogger_v1
2021-03-29 datalogger_v2
2021-03-30 datalogger_v3
2021-05-25 update instrucciones ftpd
2021-06-04 datalogger_ads_v2
2021-08-09 index de html
2021-08-20 avance_css
2021-08-24 formato_intel
2021-11-08 proceso
2021-11-16 entrevista
2021-11-16 entrevista2
2021-11-26 pre_examen
2021-11-29 preinter
2022-01-21 efirma
2022-02-28 ras y fpga
2022-02-28 ms5803
2022-10-17 delete
    delete
2022-10-18 update2.0
